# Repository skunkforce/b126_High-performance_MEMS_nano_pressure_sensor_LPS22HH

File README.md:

# edgy_board number b126
This design is part of the [edgy board project](https://github.com/skunkforce/edgy_boards).

# getting started
This repository uses submodules. After cloning use the command 

```$ git submodule update --init --recursive```

to pull the submodules before opening the project with kicad. 

# Tests
Tests can be found in [TESTS.md](TESTS.md)

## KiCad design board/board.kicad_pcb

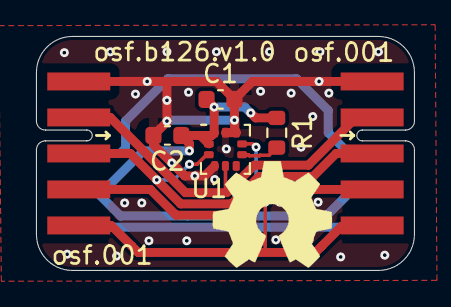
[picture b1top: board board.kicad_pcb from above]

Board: 2 copper layers, 21.0 x 13.0 mm, 7 parts (0 on the bottom side), 9 nets.

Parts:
C1, C2: 100nF; C_0603_1608Metric
J1: 001_I2C; on_edge_2x05_device
J2: 001_I2C; on_edge_2x05_host
LOGO1: Logo_Open_Hardware_Small; OSHW-Symbol_6.7x6mm_SilkScreen
R1: 0R; R_0603_1608Metric
U1: LPS25HB; ST_HLGA-10_2.5x2.5mm_P0.6mm_LayoutBorder3x2y

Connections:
/pressure/INT: J1.5 (INT), J2.5 (INT), U1.7 (INT_DRDY)
/pressure/SCL: J1.3 (SCL), J2.3 (SCL), U1.2 (SCL/SCLK)
/pressure/SDA: J1.2 (SDA), J2.2 (SDA), U1.4 (SDA/MOSI)
/pressure/VDD: C1.1, C2.1, J1.9 (3.3V), J2.9 (3.3V), R1.1, U1.1 (VDDio), U1.10 (VDD)
/pressure/~CS: R1.2, U1.6 (~CS)
GND: C1.2, C2.2, J1.1 (GND), J2.1 (GND), U1.3 (GND), U1.8 (GND), U1.9 (GND)
unnamed: J1.4 (CS/EN), J2.4 (CS/EN)
unnamed: J1.8 (~RESET), J2.8 (~RESET)
unnamed: J1.10 (5V), J2.10 (5V)

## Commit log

2023-04-15 initial
2023-05-28 added ground plane
